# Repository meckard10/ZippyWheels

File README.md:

# ZippyWheels
Clemson Senior Design II Project

Melody Eckard, Xander Hagler, Nitya Harikumar, Karlee Kesler, Covington Loftus

## Overview

Remote-controlled roller skates project.

## Folders

1. /Pi PICOW C Code
	- contains C/C++ code for a Raspberry Pi Pico W

2. /Remote Design
	- contains PCB design files and 3D design for remote body
	- Autodesk EAGLE CAD, KiCAD, and SOLIDWORKS were used for these files

3. /Skate Design
	- contains 3D design files for skate body
	- Autodesk Inventor was used for these files

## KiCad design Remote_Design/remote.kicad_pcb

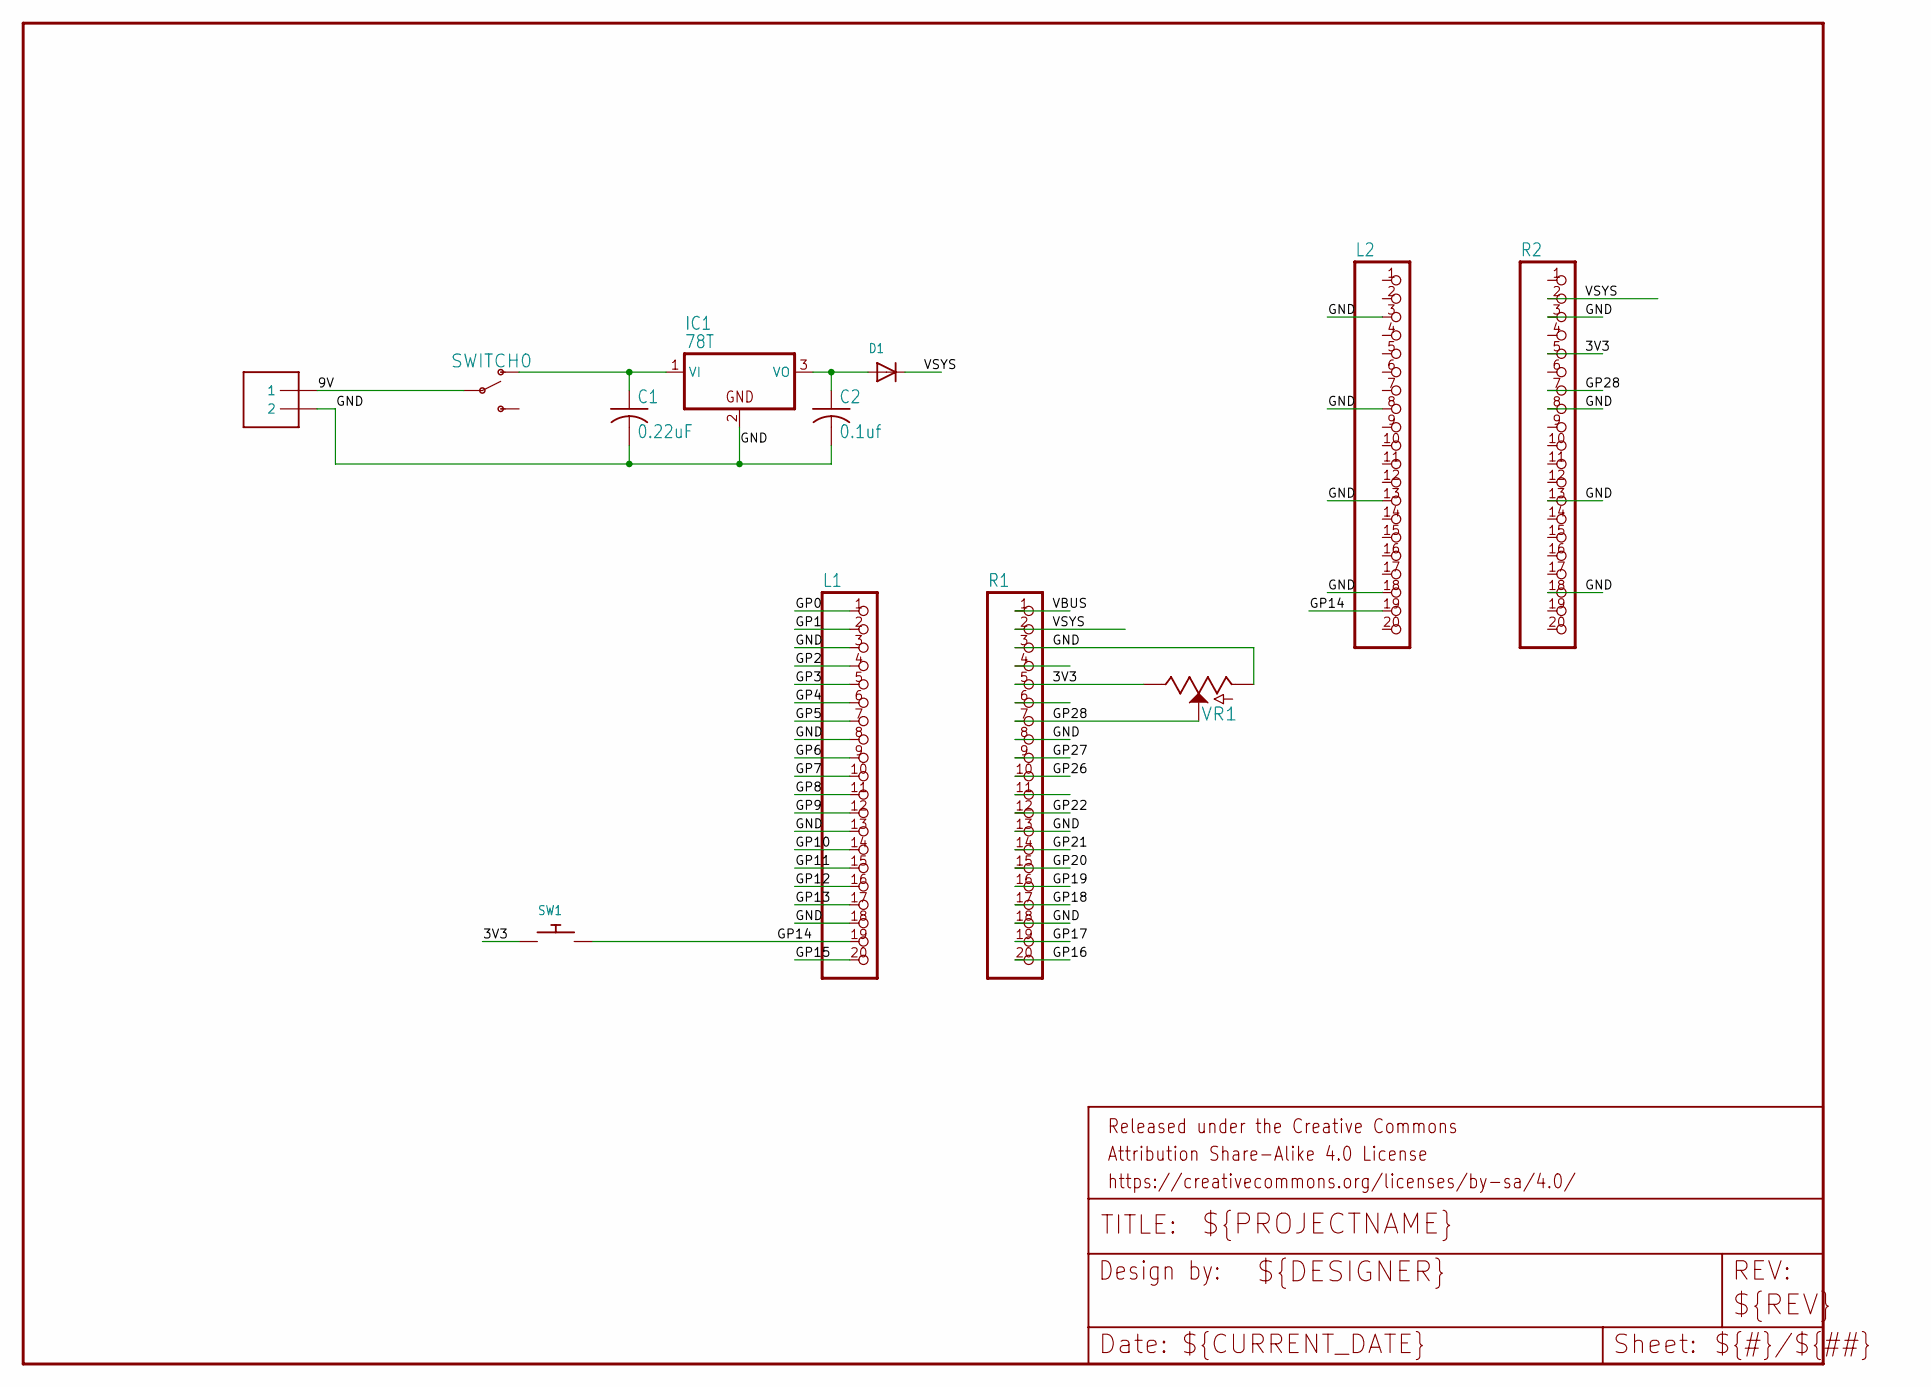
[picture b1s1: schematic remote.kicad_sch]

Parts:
C1: 0.22uF; C050-025X075
C2: 0.1uf; C050-025X075
D1: DIODEDO-1N4148; DO-1N4148
FRAME1: FRAME-LETTER; CREATIVE_COMMONS
IC1: 78T; TO220H
L1, L2: PINHD-1X20; 1X20
R1, R2: PINHD-1X20; 1X20
SW1: SWITCH_PUSHBUTTONEVQ-PE; TACT_PANA-EVQ
SWITCH0: SWITCH-SPDT-PTH-11.6X4.0MM-LOCK; SWITCH_SPDT_PTH_11.6X4.0MM_LOCK
UNK9VBAT0: 1X2-3.5MM
VR1: 10k; POT-PTH-ALPS

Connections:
3V3: R1.5, R2.5, SW1.P$1, VR1.P$1 (E)
9V: SWITCH0.2, UNK9VBAT0.1
GND: C1.2, C2.2, IC1.2 (GND), L1.3, L1.8, L1.13, L1.18, L2.3, L2.8, L2.13, L2.18, R1.3, R1.8, R1.13, R1.18, R2.3, R2.8, R2.13, R2.18, UNK9VBAT0.2, VR1.P$3 (A)
GP0: L1.1
GP1: L1.2
GP2: L1.4
GP3: L1.5
GP4: L1.6
GP5: L1.7
GP6: L1.9
GP7: L1.10
GP8: L1.11
GP9: L1.12
GP10: L1.14
GP11: L1.15
GP12: L1.16
GP13: L1.17
GP14: L1.19, L2.19, SW1.P$2
GP15: L1.20
GP16: R1.20
GP17: R1.19
GP18: R1.17
GP19: R1.16
GP20: R1.15
GP21: R1.14
GP22: R1.12
GP26: R1.10
GP27: R1.9
GP28: R1.7, R2.7, VR1.P$2 (S)
unnamed: C2.1, D1.A, IC1.3 (VO)
unnamed: C1.1, IC1.1 (VI), SWITCH0.1 (O)
VBUS: R1.1
VSYS: D1.C, R1.2, R2.2

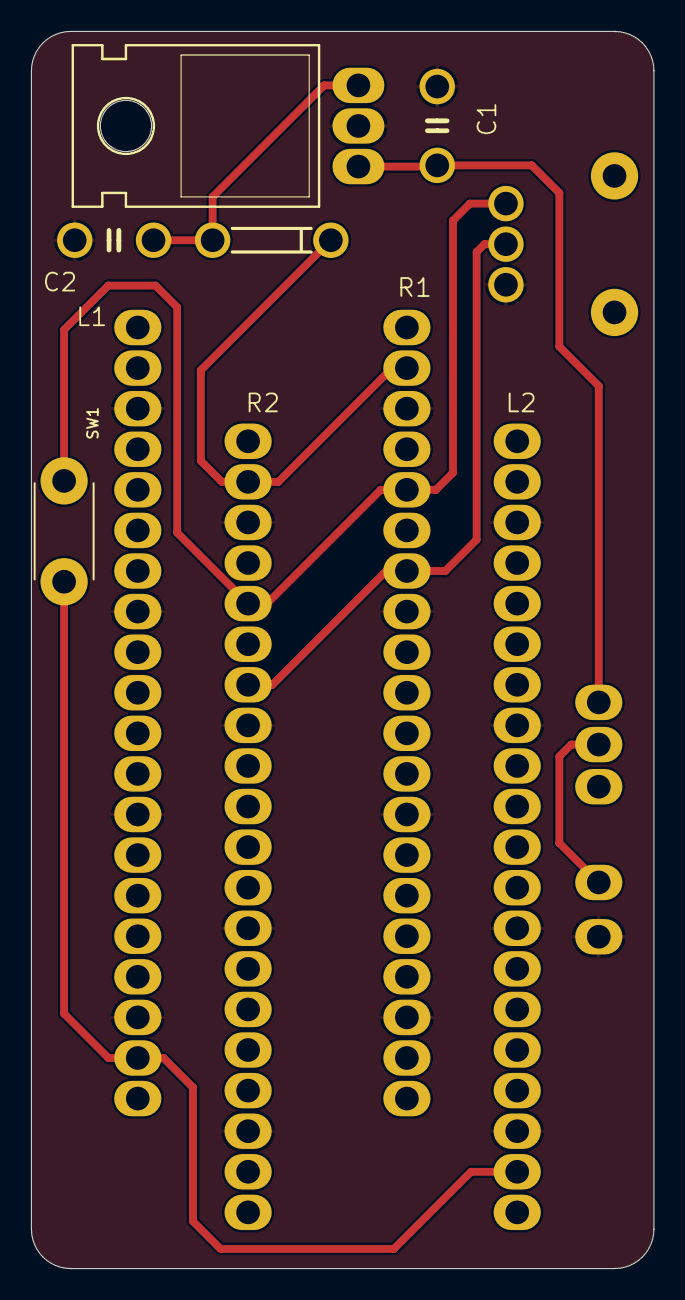
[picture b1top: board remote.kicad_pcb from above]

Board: 2 copper layers, 40.1 x 79.8 mm, 13 parts (0 on the bottom side), 8 nets.

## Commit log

2024-09-18 wrote README and added blink examples
2024-09-18 Changed folder name
2024-09-18 hello_world example
2024-09-23 added Bluetooth stuff
2024-10-22 Modified PWM signal and made som setting changes to bluetooth
2024-10-30 Update writer.cpp, add button
2024-11-15 Update reader.cpp, get hall sensor readings
2024-11-15 Update writer.cpp, change scaling factor of potentiometer reading (max of 2^16)
2024-12-12 Update reader.cpp, hall sensor feedback
2025-04-04 added physical designs

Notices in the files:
Remote_Design/remote.kicad_sch:
https://creativecommons.org/licenses/by-sa/4.0
Released under the Creative Commons
parts and their libraries:
Released under the Creative Commons Attribution Share-Alike 4.0 License
